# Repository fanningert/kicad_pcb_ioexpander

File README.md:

# I²C IO-Expander

Core goal is a pcb with the same pin outs, but with different i²C IO Expander. Castellated holes with secondary pin header holes are added, for direct PCB soldering. Secondary pin header holes are placed in a matrix of 2,54 mm (100 mils). Because of the fixed pin layout of the pcb, I created the boards in a four layer design.

# Versions

## SX1509

## PCA9685

## Features

* Solder pads for I²C address
* Solder pads for I²C Pull-Up Resistor

## ToDos

* Create working GitHub workflow to create releases
* Optimize GitHub workflow for a more generic solution (no modification, when adding a new board)

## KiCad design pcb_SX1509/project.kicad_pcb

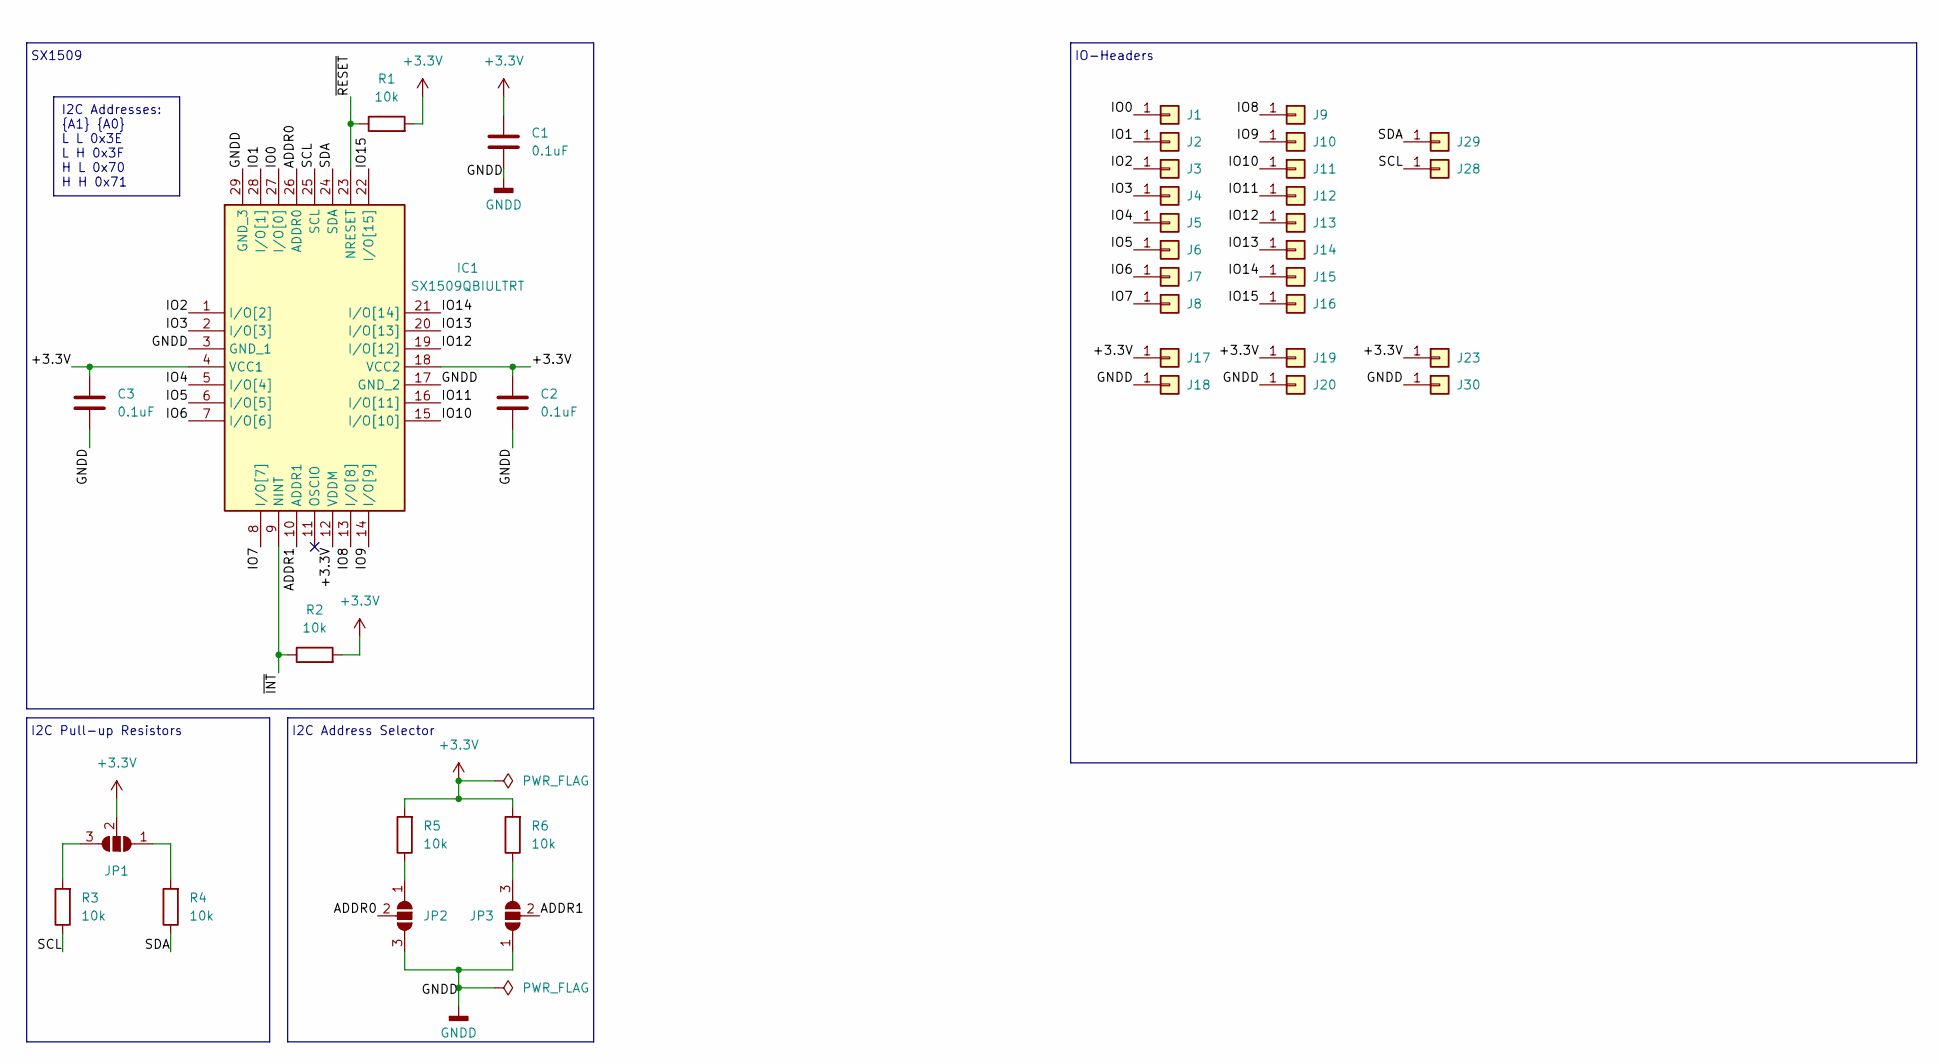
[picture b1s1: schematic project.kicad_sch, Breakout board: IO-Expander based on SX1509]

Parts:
C1, C2, C3: 0.1uF; C_0402_1005Metric_Pad0.74x0.62mm_HandSolder
IC1: SX1509QBIULTRT; QFN40P400X400X60-29N-D; Mouser Part Number 947-SX1509QBIULTRT
J1, J2, J3, J4, J5, J6, J7, J8, J9, J10, J11, J12, J13, J14, J15, J16, J17, J18, J19, J20, J23, J28, J29, J30: Castellated_Hole02
JP1, JP2, JP3: SolderJumper_3_Open; SolderJumper-3_P1.3mm_Open_RoundedPad1.0x1.5mm
R1, R2, R3, R4, R5, R6: 10k; R_0402_1005Metric_Pad0.72x0.64mm_HandSolder

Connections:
+3.3V: C1.1, C2.1, C3.1, IC1.4 (VCC1), IC1.12 (VDDM), IC1.18 (VCC2), J17.1, J19.1, J23.1, JP1.2 (C), R1.2, R2.2, R5.2, R6.2
/ADDR0: IC1.26 (ADDR0), JP2.2 (C)
/ADDR1: IC1.10 (ADDR1), JP3.2 (C)
/IO0: IC1.27 (I/O[0]), J1.1
/IO1: IC1.28 (I/O[1]), J2.1
/IO2: IC1.1 (I/O[2]), J3.1
/IO3: IC1.2 (I/O[3]), J4.1
/IO4: IC1.5 (I/O[4]), J5.1
/IO5: IC1.6 (I/O[5]), J6.1
/IO6: IC1.7 (I/O[6]), J7.1
/IO7: IC1.8 (I/O[7]), J8.1
/IO8: IC1.13 (I/O[8]), J9.1
/IO9: IC1.14 (I/O[9]), J10.1
/IO10: IC1.15 (I/O[10]), J11.1
/IO11: IC1.16 (I/O[11]), J12.1
/IO12: IC1.19 (I/O[12]), J13.1
/IO13: IC1.20 (I/O[13]), J14.1
/IO14: IC1.21 (I/O[14]), J15.1
/IO15: IC1.22 (I/O[15]), J16.1
/SCL: IC1.25 (SCL), J28.1, R3.1
/SDA: IC1.24 (SDA), J29.1, R4.1
/~INT: IC1.9 (NINT), R2.1
/~RESET: IC1.23 (NRESET), R1.1
GNDD: C1.2, C2.2, C3.2, IC1.3 (GND_1), IC1.17 (GND_2), IC1.29 (GND_3), J18.1, J20.1, J30.1, JP2.3 (B), JP3.1 (A)
unnamed: JP1.1 (A), R4.2
unnamed: JP1.3 (B), R3.2
unnamed: JP2.1 (A), R5.1
unnamed: JP3.3 (B), R6.1

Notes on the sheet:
I2C Addresses: {A1} {A0} L L 0x3E L H 0x3F H L 0x70 H H 0x71
IO-Headers
I2C Address Selector
I2C Pull-up Resistors
SX1509

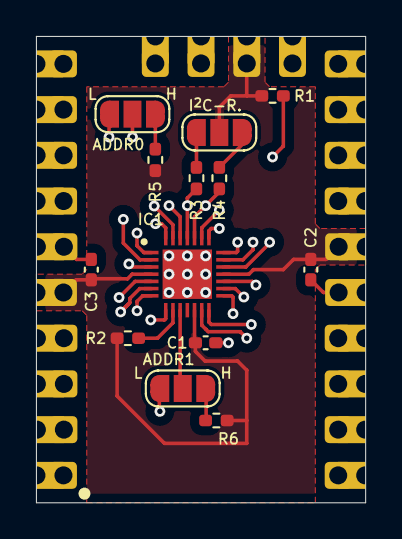
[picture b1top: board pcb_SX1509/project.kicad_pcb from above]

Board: 4 copper layers, 18.3 x 25.9 mm, 38 parts (1 on the bottom side), 28 nets.

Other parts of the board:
QR*****: https://github.com/fanningert/kicad_pcb_ioexpander; //github.com/fanningert/kicad_pcb_ioexpander

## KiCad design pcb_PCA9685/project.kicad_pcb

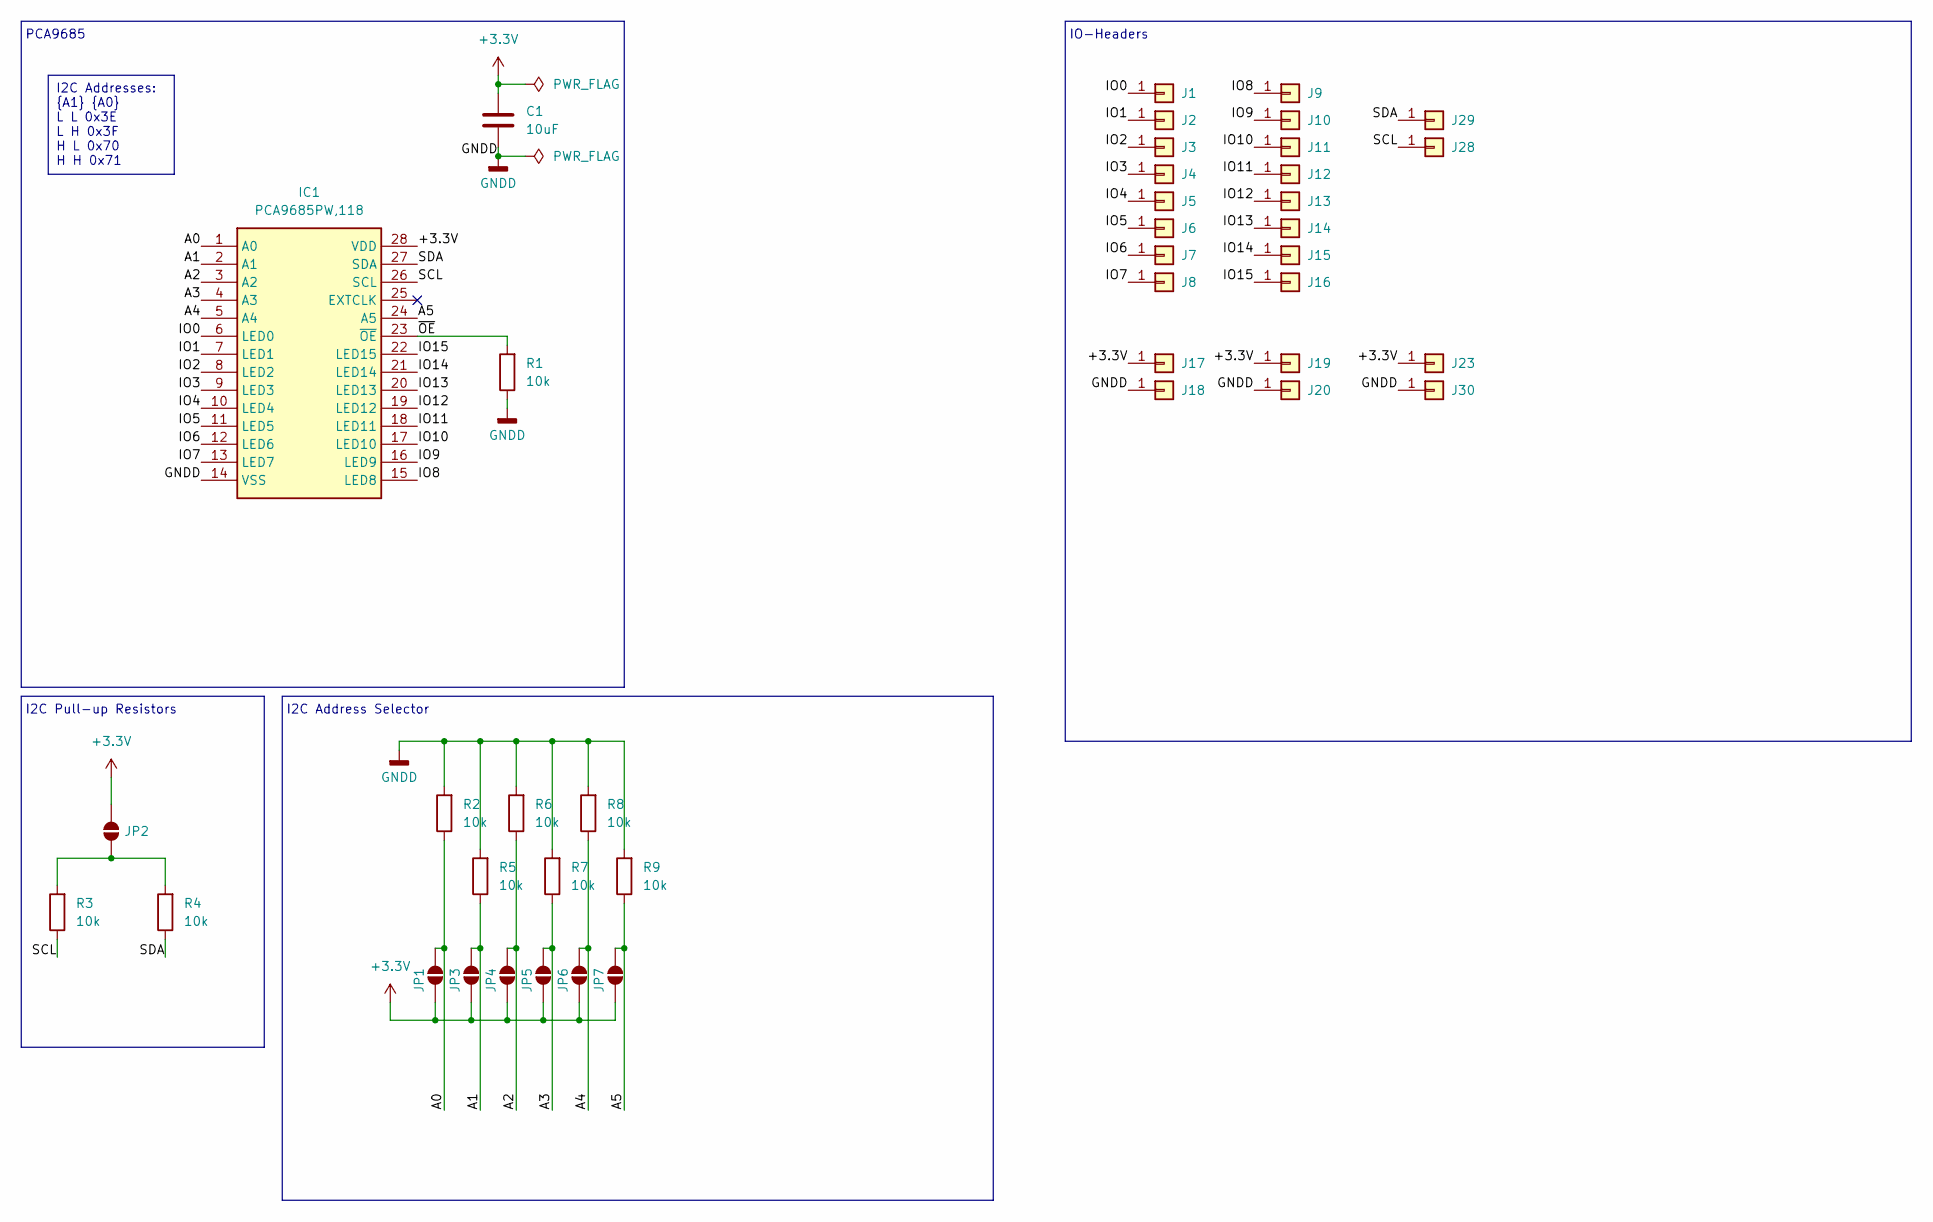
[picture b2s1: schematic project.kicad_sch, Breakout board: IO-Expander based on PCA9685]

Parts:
C1: 10uF; C_0402_1005Metric_Pad0.74x0.62mm_HandSolder
IC1: PCA9685PW,118; SOP65P640X110-28N; Mouser Part Number 771-PCA9685PW,118
J1, J2, J3, J4, J5, J6, J7, J8, J9, J10, J11, J12, J13, J14, J15, J16, J17, J18, J19, J20, J23, J28, J29, J30: Castellated_Hole02
JP1, JP2, JP3, JP4, JP5, JP6, JP7: SolderJumper_2_Open; SolderJumper-2_P1.3mm_Open_TrianglePad1.0x1.5mm
R1, R2, R3, R4, R5, R6, R7, R8, R9: 10k; R_0402_1005Metric_Pad0.72x0.64mm_HandSolder

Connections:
+3.3V: C1.1, IC1.28 (VDD), J17.1, J19.1, J23.1, JP1.2 (B), JP2.2 (B), JP3.2 (B), JP4.2 (B), JP5.2 (B), JP6.2 (B), JP7.2 (B)
/A0: IC1.1 (A0), JP1.1 (A), R2.1
/A1: IC1.2 (A1), JP3.1 (A), R5.1
/A2: IC1.3 (A2), JP4.1 (A), R6.1
/A3: IC1.4 (A3), JP5.1 (A), R7.1
/A4: IC1.5 (A4), JP6.1 (A), R8.1
/A5: IC1.24 (A5), JP7.1 (A), R9.1
/IO0: IC1.6 (LED0), J1.1
/IO1: IC1.7 (LED1), J2.1
/IO2: IC1.8 (LED2), J3.1
/IO3: IC1.9 (LED3), J4.1
/IO4: IC1.10 (LED4), J5.1
/IO5: IC1.11 (LED5), J6.1
/IO6: IC1.12 (LED6), J7.1
/IO7: IC1.13 (LED7), J8.1
/IO8: IC1.15 (LED8), J9.1
/IO9: IC1.16 (LED9), J10.1
/IO10: IC1.17 (LED10), J11.1
/IO11: IC1.18 (LED11), J12.1
/IO12: IC1.19 (LED12), J13.1
/IO13: IC1.20 (LED13), J14.1
/IO14: IC1.21 (LED14), J15.1
/IO15: IC1.22 (LED15), J16.1
/SCL: IC1.26 (SCL), J28.1, R3.1
/SDA: IC1.27 (SDA), J29.1, R4.1
/~OE: IC1.23 (~OE), R1.2
GNDD: C1.2, IC1.14 (VSS), J18.1, J20.1, J30.1, R1.1, R2.2, R5.2, R6.2, R7.2, R8.2, R9.2
unnamed: JP2.1 (A), R3.2, R4.2

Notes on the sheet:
I2C Addresses: {A1} {A0} L L 0x3E L H 0x3F H L 0x70 H H 0x71
IO-Headers
I2C Address Selector
I2C Pull-up Resistors
PCA9685

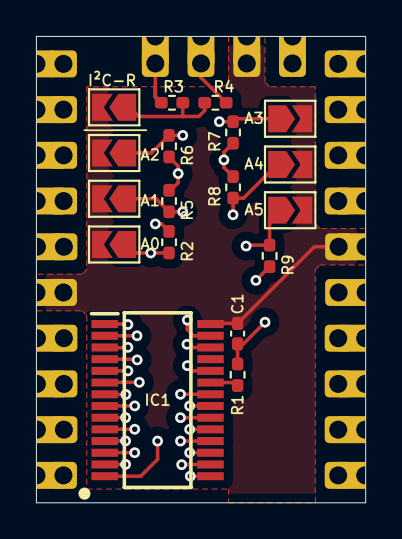
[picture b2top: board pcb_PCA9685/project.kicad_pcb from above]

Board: 4 copper layers, 18.3 x 25.9 mm, 43 parts (1 on the bottom side), 28 nets.

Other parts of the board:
QR*****: https://github.com/fanningert/kicad_pcb_ioexpander; //github.com/fanningert/kicad_pcb_ioexpander

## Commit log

2024-06-01 Add ignore file
2024-06-01 Cleanup
2024-06-01 Update kitbot config
2024-06-02 Update PCB with infos
2024-06-02 Correct README
2024-06-02 Optimize pcb layout
2024-06-02 Correct bug in README and update images
2024-06-02 Standard output pin design for SX1509 PCB and add a new variant based on PCA9685
2024-06-02 removed space in directory name
2024-06-02 Update workflow
2024-06-03 Update PCB for PCA9685
2024-06-03 Add barcode with the GitHub repository URL on the backsite of the PCBs
2024-06-03 Replace QRCode with better version
2024-06-03 Update README and doc assets
2024-06-04 Remove connector on own side
2024-06-04 Updates doc images
2024-06-04 Replace resistor array throw single resistor for reducing vias dn easy component selection
2024-06-04 Remove qrcode from bom
2024-06-09 Correct workflow bug
2024-06-09 Add panelize
2024-06-09 Correct bugin panlize config
2024-06-09 Add debug level to panelize step for analizing
2024-06-09 Add generation of extra files for panlized PCB
2024-06-09 Correct bug in panelize workflow
2024-06-09 Limit parallel strategie to one running job
2024-06-09 Change owner before upload artifact
2024-06-09 Correct some warnings and missing 3D step files
2024-06-09 Removed not needed text
2024-06-09 Edit panelize config
2024-06-09 Change position of fiducials and tooling
2024-06-09 Add revision number to PCB
2024-06-12 Correct kibot for four layer
2024-06-15 Test kiBot configuration with multi layer PCB
